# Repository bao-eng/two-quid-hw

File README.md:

# two-quid-hw
Miniature nRF54L-based board with IMU/RGB LED/button/buzzer/2032 battery

## Features
- Nordic nRF54L15 wireless SoC
- ST LSM6DSL 6DoF IMU
- RGB LED indicator
- Push-button
- 4kHz buzzer
- Powered by replaceable 2032 coin cell battery
- £2 coin-sized PCB(D=28.4mm)
- ~6.5mm overall PCBA height
- Sane 0402 components
- Breakaway piece with debugging connectors: \
    10-pin [Cortex-Debug](https://developer.arm.com/documentation/101416/0100/Hardware-Description/Target-Interfaces/Cortex-Debug--10-pin-) (1.27mm pitch) connector for debugging using nRF54L15-DK+[IDC cable](https://www.adafruit.com/product/1675) or J-Link+[ARM-JTAG-20-10 cable](https://www.olimex.com/Products/ARM/JTAG/ARM-JTAG-20-10/) \
    2x3-pin (2.54mm pitch) connectors for jumper wires

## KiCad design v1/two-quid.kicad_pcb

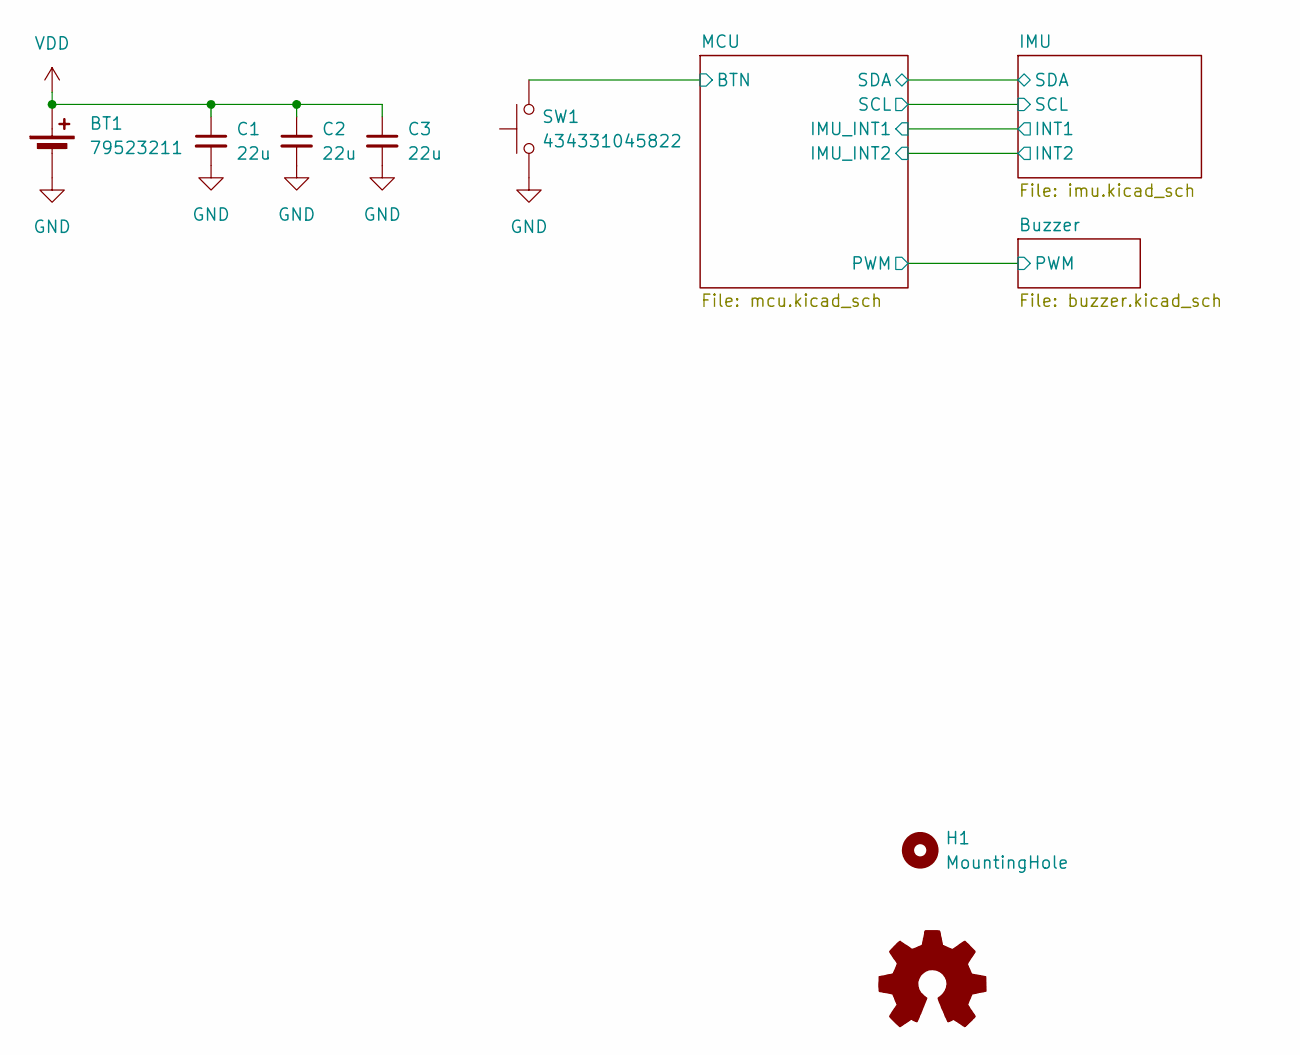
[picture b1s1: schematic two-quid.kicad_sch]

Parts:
BT1: 79523211; BatteryHolder_WE_79523211_1x2016,2020,2025,2032
C1, C2, C3: 22u; C_0805_2012Metric; MPN 885012107005
H1: MountingHole; MountingHole_2.2mm_M2
SW1: 434331045822
SYM1: Logo_Open_Hardware_Small; OSHW-Logo_5.7x6mm_SilkScreen

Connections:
/MCU/BTN: SW1.2; also elsewhere on the board
GND: BT1.2 (-), C1.2, C2.2, C3.2, SW1.1; also elsewhere on the board
VDD: BT1.1 (+), C1.1, C2.1, C3.1; also elsewhere on the board

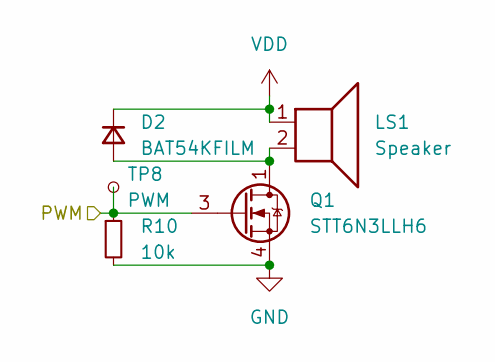
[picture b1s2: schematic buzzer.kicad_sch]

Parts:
D2: BAT54KFILM; D_SOD-523
LS1: Speaker; OWMB-404020SA-40-17
Q1: STT6N3LLH6; SOT-23-6
R10: 10k; R_0402_1005Metric; MPN 560112110020
TP8: PWM; TestPoint_Pad_D1.0mm

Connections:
/Buzzer/PWM: Q1.3 (G), R10.1, TP8.1; also elsewhere on the board
GND: Q1.4 (S), R10.2; also elsewhere on the board
unnamed: D2.2 (A), LS1.2, Q1.1 (D), Q1.2 (D), Q1.5 (D), Q1.6 (D)
VDD: D2.1 (K), LS1.1; also elsewhere on the board

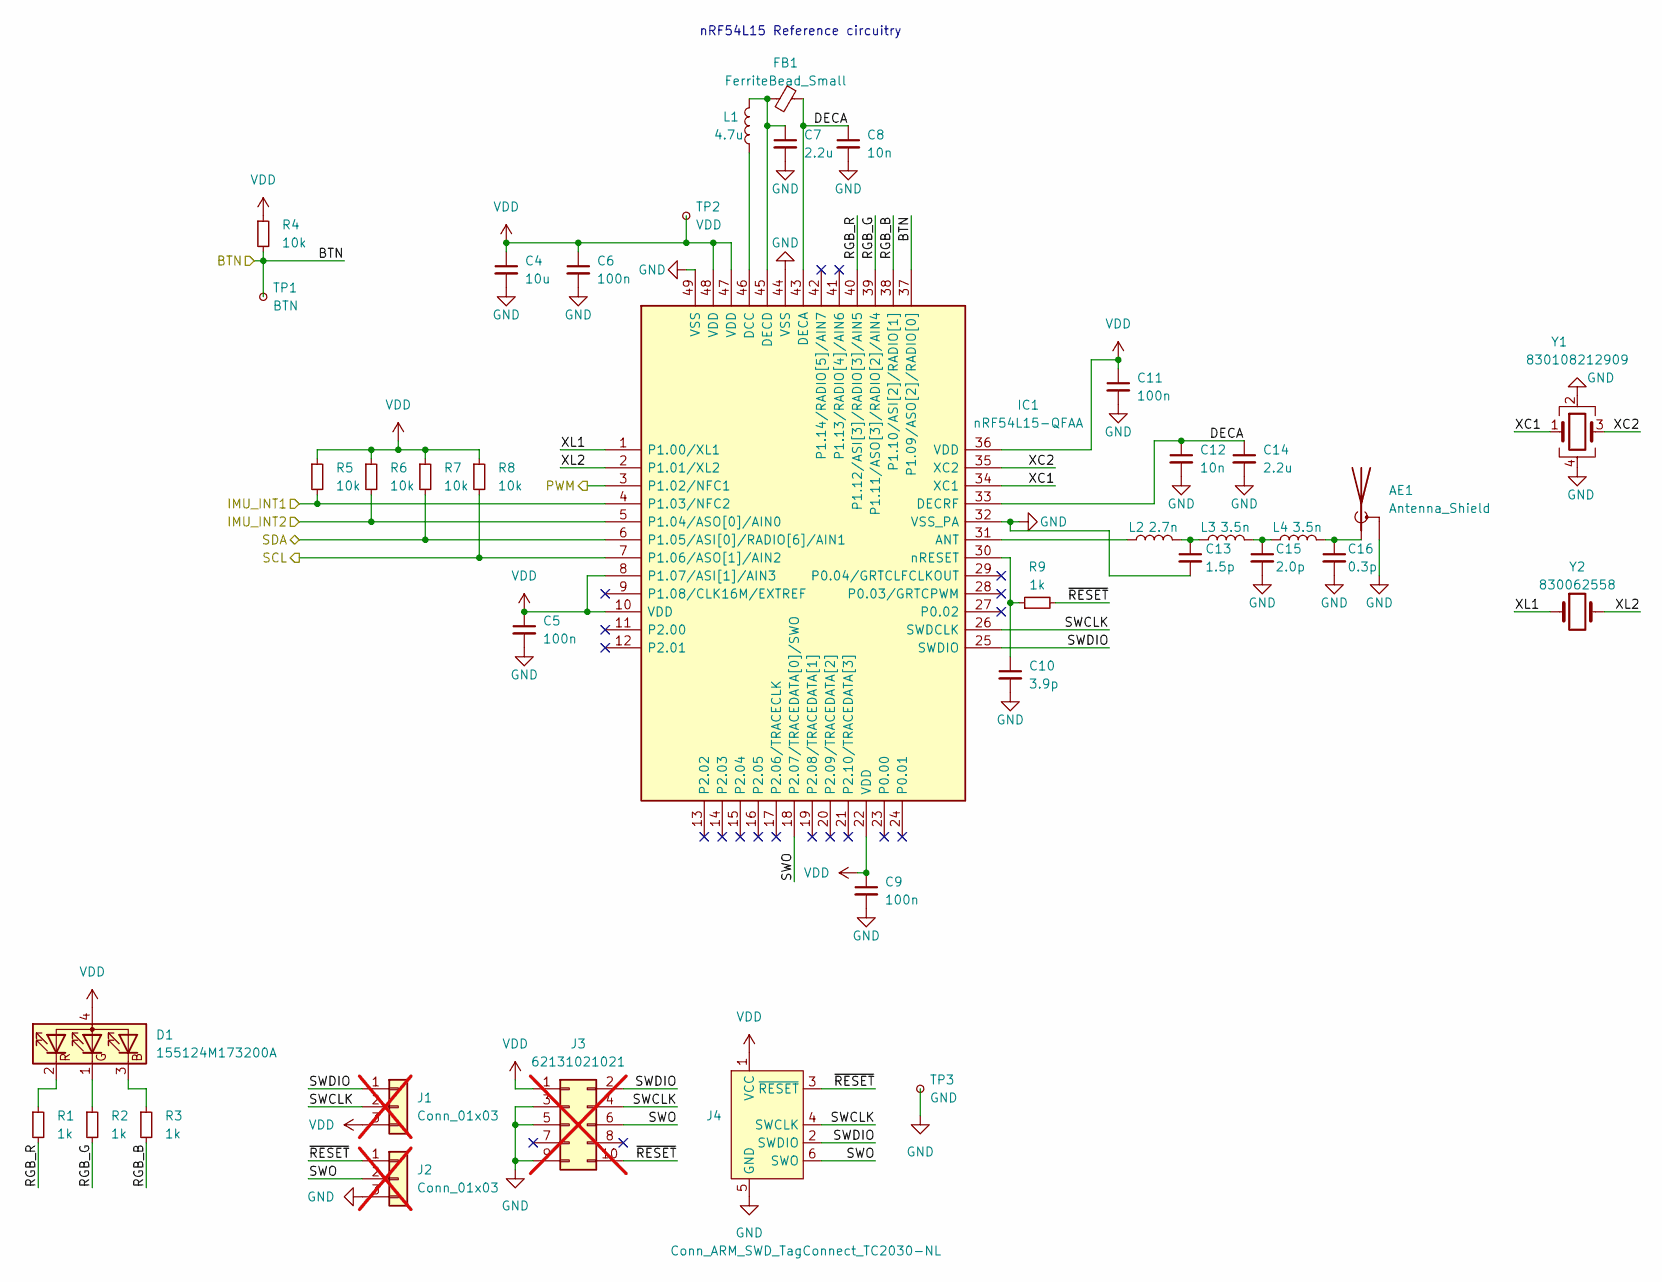
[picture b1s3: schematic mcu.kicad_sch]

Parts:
AE1: Antenna_Shield; Texas_SWRA117D_2.4GHz_Left
C4: 10u; C_0402_1005Metric; MPN 885012105020
C5, C6, C9, C11: 100n; C_0402_1005Metric; MPN 885012205018
C7, C14: 2.2u; C_0402_1005Metric; MPN 885012105013
C8, C12: 10n; C_0402_1005Metric; MPN 885012205012
C10: 3.9p; C_0402_1005Metric; MPN 885012205018
C13: 1.5p; C_0402_1005Metric; MPN CBR04C159A3GAC/GJM1555C1H1R5WB01D
C15: 2.0p; C_0402_1005Metric; MPN GJM1555C1H2R0WB01D
C16: 0.3p; C_0402_1005Metric; MPN GJM1555C1HR30BB01D
D1: 155124M173200A
FB1: FerriteBead_Small; L_0402_1005Metric; MPN 74279271
IC1: nRF54L15-QFAA; QFN-48-1EP_6x6mm_P0.4mm_EP4.66x4.66mm; Manufacturer_Part_Number nRF54L15-QFAA
J1, J2: Conn_01x03; PinHeader_1x03_P2.54mm_Vertical; not fitted
J3: 62131021021; PinHeader_2x05_P1.27mm_Vertical_SMD; not fitted
J4: Conn_ARM_SWD_TagConnect_TC2030-NL; Tag-Connect_TC2030-IDC-NL_2x03_P1.27mm_Vertical
L1: 4.7u; L_0603_1608Metric; MPN MLZ1608M4R7WT000
L2: 2.7n; L_0402_1005Metric; MPN 744765027A
L3: 3.5n; L_0402_1005Metric; MPN LQG15WH3N5B02D
L4: 3.5n; L_0402_1005Metric; MPN LQG15WH3N5B02D/MHQ1005075HA3N5BTD25
R1, R2, R3, R9: 1k; R_0402_1005Metric; MPN 560112110012
R4, R5, R6, R7, R8: 10k; R_0402_1005Metric; MPN 560112110020
TP1: BTN; TestPoint_Pad_D1.0mm
TP2: VDD; TestPoint_Pad_D1.0mm
TP3: GND; TestPoint_Pad_D1.0mm
Y1: 830108212909; Crystal_SMD_2016-4Pin_2.0x1.6mm
Y2: 830062558; Crystal_SMD_2012-2Pin_2.0x1.2mm

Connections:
/Buzzer/PWM: IC1.3 (P1.02/NFC1); also elsewhere on the board
/IMU/INT1: IC1.4 (P1.03/NFC2), R5.2; also elsewhere on the board
/IMU/INT2: IC1.5 (P1.04/ASO[0]/AIN0), R6.2; also elsewhere on the board
/IMU/SCL: IC1.7 (P1.06/ASO[1]/AIN2), R8.2; also elsewhere on the board
/IMU/SDA: IC1.6 (P1.05/ASI[0]/RADIO[6]/AIN1), R7.2; also elsewhere on the board
/MCU/BTN: IC1.37 (P1.09/ASO[2]/RADIO[0]), R4.2, TP1.1; also elsewhere on the board
/MCU/DECA: C8.1, C12.1, C14.1, FB1.1, IC1.33 (DECRF), IC1.43 (DECA)
/MCU/RGB_B: IC1.38 (P1.10/ASI[2]/RADIO[1]), R3.2
/MCU/RGB_G: IC1.39 (P1.11/ASO[3]/RADIO[2]/AIN4), R2.2
/MCU/RGB_R: IC1.40 (P1.12/ASI[3]/RADIO[3]/AIN5), R1.2
/MCU/SWCLK: IC1.26 (SWDCLK), J1.2, J3.4, J4.4 (SWCLK)
/MCU/SWDIO: IC1.25 (SWDIO), J1.1, J3.2, J4.2 (SWDIO)
/MCU/SWO: IC1.18 (P2.07/TRACEDATA[0]/SWO), J2.2, J3.6, J4.6 (SWO)
/MCU/XC1: IC1.34 (XC1), Y1.1
/MCU/XC2: IC1.35 (XC2), Y1.3
/MCU/XL1: IC1.1 (P1.00/XL1), Y2.1
/MCU/XL2: IC1.2 (P1.01/XL2), Y2.2
/MCU/~RESET: J2.1, J3.10, J4.3 (~RESET), R9.2
GND: AE1.2 (Shield), C4.2, C5.2, C6.2, C7.2, C8.2, C9.2, C10.2, C11.2, C12.2, C13.2, C14.2, C15.2, C16.2, IC1.32 (VSS_PA), IC1.44 (VSS), IC1.49 (VSS), J2.3, J3.3, J3.5, J3.9, J4.5 (GND), TP3.1, Y1.2, Y1.4; also elsewhere on the board
unnamed: AE1.1 (A), C16.1, L4.2
unnamed: C13.1, L2.2, L3.1
unnamed: C15.1, L3.2, L4.1
unnamed: D1.3 (BK), R3.1
unnamed: D1.1 (GK), R2.1
unnamed: D1.2 (RK), R1.1
unnamed: IC1.31 (ANT), L2.1
unnamed: IC1.46 (DCC), L1.1
unnamed: C7.1, FB1.2, IC1.45 (DECD), L1.2
unnamed: C10.1, IC1.30 (nRESET), R9.1
VDD: C4.1, C5.1, C6.1, C9.1, C11.1, D1.4 (A), IC1.8 (P1.07/ASI[1]/AIN3), IC1.10 (VDD), IC1.22 (VDD), IC1.36 (VDD), IC1.47 (VDD), IC1.48 (VDD), J1.3, J3.1, J4.1 (VCC), R4.1, R5.1, R6.1, R7.1, R8.1, TP2.1; also elsewhere on the board

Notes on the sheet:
nRF54L15 Reference circuitry

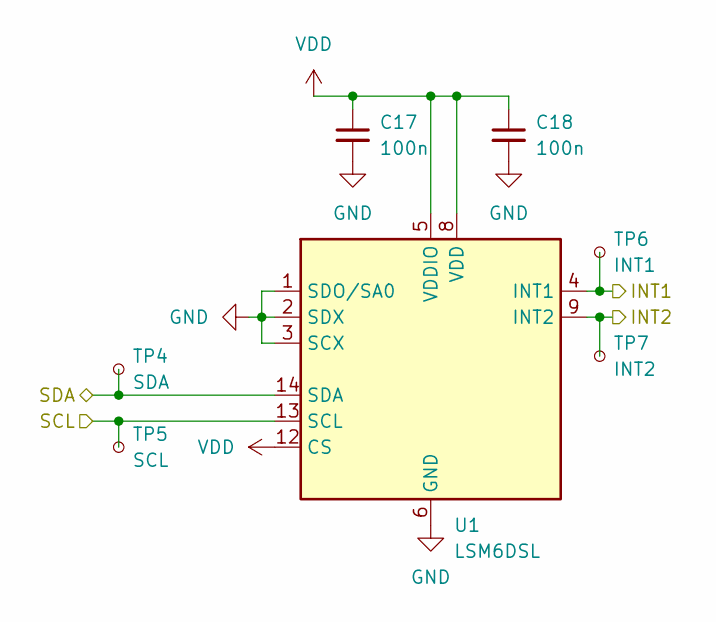
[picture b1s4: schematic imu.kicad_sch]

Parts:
C17, C18: 100n; C_0402_1005Metric; MPN 885012205018
TP4: SDA; TestPoint_Pad_D1.0mm
TP5: SCL; TestPoint_Pad_D1.0mm
TP6: INT1; TestPoint_Pad_D1.0mm
TP7: INT2; TestPoint_Pad_D1.0mm
U1: LSM6DSL; LGA-14_3x2.5mm_P0.5mm_LayoutBorder3x4y

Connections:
/IMU/INT1: TP6.1, U1.4 (INT1); also elsewhere on the board
/IMU/INT2: TP7.1, U1.9 (INT2); also elsewhere on the board
/IMU/SCL: TP5.1, U1.13 (SCL); also elsewhere on the board
/IMU/SDA: TP4.1, U1.14 (SDA); also elsewhere on the board
GND: C17.2, C18.2, U1.1 (SDO/SA0), U1.2 (SDX), U1.3 (SCX), U1.6 (GND), U1.7 (GND); also elsewhere on the board
VDD: C17.1, C18.1, U1.5 (VDDIO), U1.8 (VDD), U1.12 (CS); also elsewhere on the board

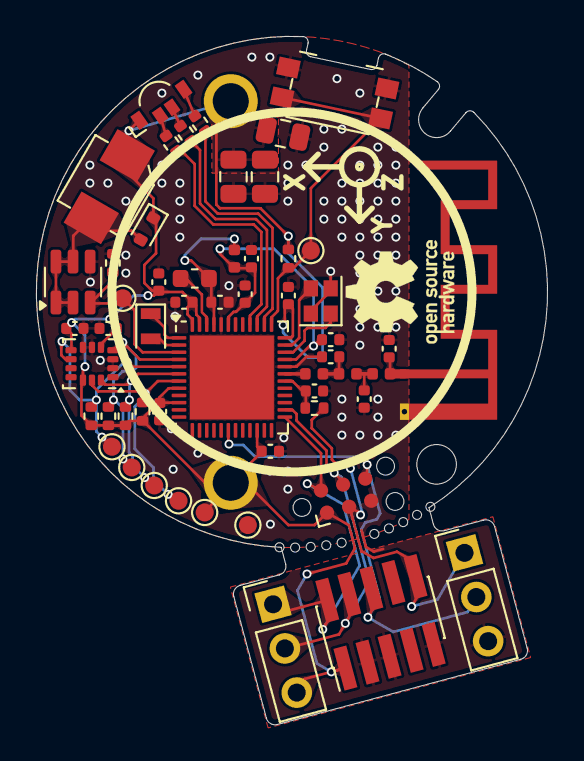
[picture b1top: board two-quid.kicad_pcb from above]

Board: 2 copper layers, 28.4 x 38.2 mm, 58 parts (1 on the bottom side), 31 nets.
